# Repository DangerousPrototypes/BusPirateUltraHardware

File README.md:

# BusPirateUltraHardware
Schematic and PCBs for Bus Pirate Ultra

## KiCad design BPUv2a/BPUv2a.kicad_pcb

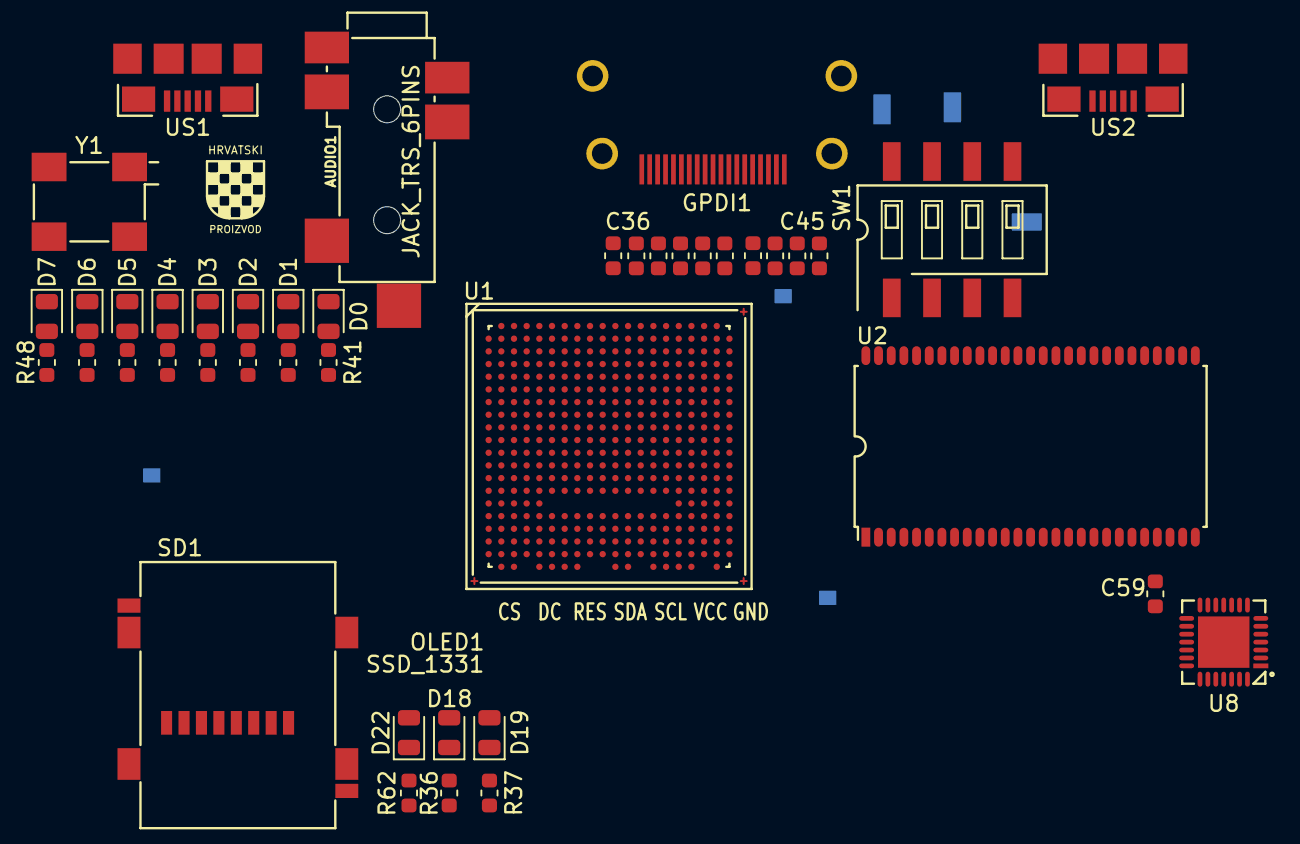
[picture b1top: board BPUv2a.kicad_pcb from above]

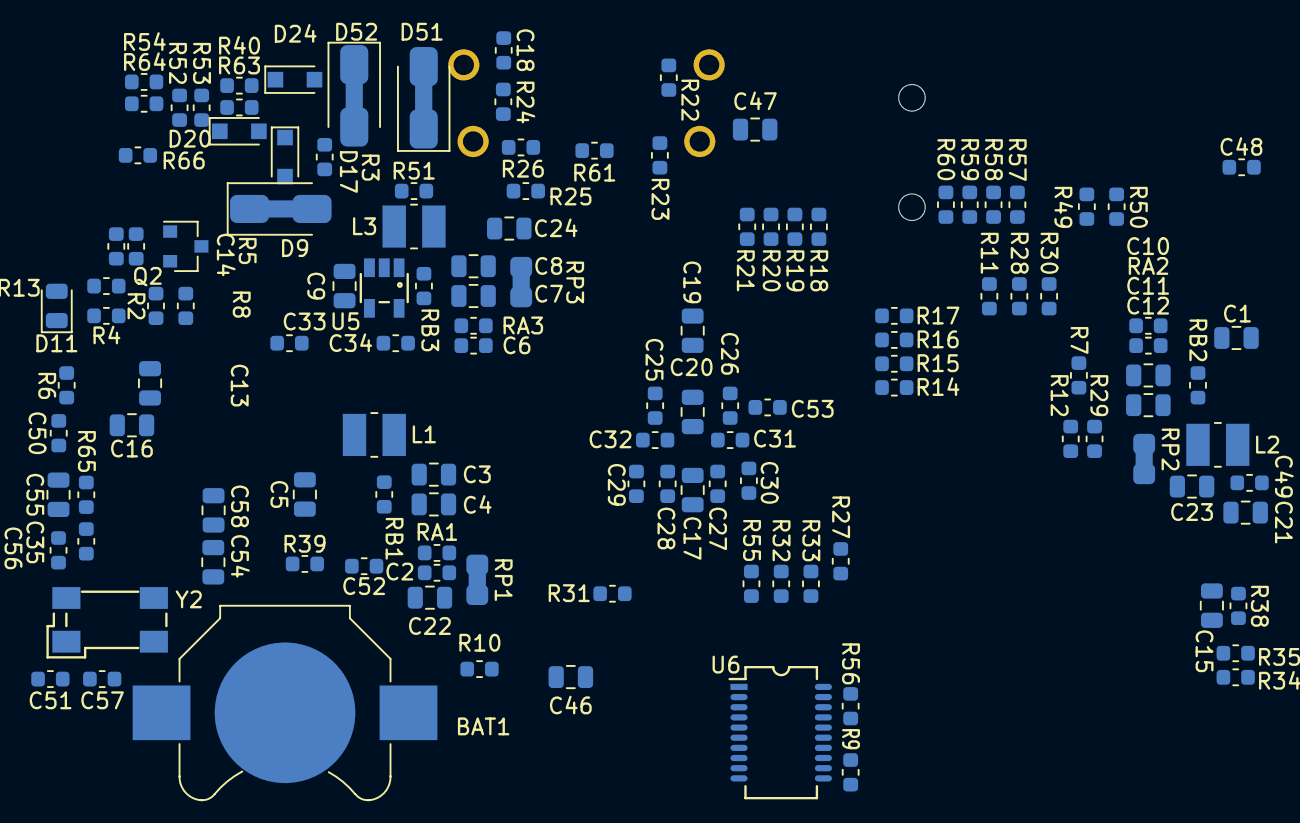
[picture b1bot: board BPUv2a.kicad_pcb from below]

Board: 4 copper layers, 171 parts (126 on the bottom side), 188 nets, no tracks yet.

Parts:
AUDIO1: JACK_TRS_6PINS; CUI_SJ-43516-SMT
BAT1: CR1225; Keystone_3000_1x12mm-CoinCell
C1, C3, C4, C5, C7, C8, C9, C11, C12, C15, C21, C54, C55, C58: 22uF; C_0805_2012Metric
C2, C6, C10, C18: 470pF; C_0603_1608Metric
C13, C16, C17, C19, C20, C22, C23, C24, C46, C47: 2.2uF; C_0805_2012Metric
C14, C36, C37, C38, C39, C40, C41, C42, C43, C44, C45, C59: 220nF; C_0603_1608Metric
C25, C26, C27, C28, C29, C30, C31, C32, C33, C34, C35, C48, C49, C50, C51, C52, C53: 22nF; C_0603_1608Metric
C56, C57: 3.3pF; C_0603_1608Metric
D0, D4, D11, D19: RED; LED_0805_2012Metric
D1, D5: ORANGE; LED_0805_2012Metric
D2, D6, D18: GREEN; LED_0805_2012Metric
D3, D7, D22: BLUE; LED_0805_2012Metric
D9, D51, D52: 0; D_SMA_Jumper_NC
D17, D24: 1N914; D_SOD-323_HandSoldering
D20: 3.6V; D_SOD-323_HandSoldering
GPDI1: GPDI-D; CONN-10029449-111RLF
HR: HR; hrvatski
L1, L2, L3: 2.2uH; L_1008_1210
OLED1: SSD_1331; oled_13xx
Q2: 2N7002; SOT-23
R2: 18k; R_0603_1608Metric
R3, R4, R25, R26, R30: 4.7k; R_0603_1608Metric
R5: 2.2M; R_0603_1608Metric
R6, R8, R14, R18, R29, R40, R54, R57, R66: 1.1k; R_0603_1608Metric
R7, R10, R17, R21, R39, R51, R60: 130; R_0603_1608Metric
R9, R13, R31, R32, R33, R34, R55, R63, R64: 15k; R_0603_1608Metric
R11, R12, R27, R28: 10k; R_0603_1608Metric
R15, R19, R35, R36, R37, R41, R42, R43, R44, R45, R46, R47, R48, R58, R61, R62, R65: 549; R_0603_1608Metric
R16, R20, R59: 270; R_0603_1608Metric
R22, R23: 3.3k; R_0603_1608Metric
R24: 100k; R_0603_1608Metric
R38: 0.47; R_0603_1608Metric
R49, R50, R52, R53: 27; R_0603_1608Metric
R56: 0; R_0603_1608Metric
RA1, RA2, RA3: 15k; R_0603_1608Metric
RB1: 18k; R_0603_1608Metric
RB2: 4.7k; R_0603_1608Metric
RB3: 3.3k; R_0603_1608Metric
RP1, RP2, RP3: 0; R_0805_2012Metric_Pad1.29x1.40mm_HandSolder_Jumper_NC
SD1: SCHD3A0100; SCHD3A100
SW1: SW_DIP_x04; SW_DIP_x4_W8.61mm_Slide_LowProfile
U1: LFE5U-85F-6BG381C; BGA-381_pitch0.8mm_dia0.4mm
U2: MT48LC16M16A2TG; TSOP54
U5: TLV62569DBV; TSOT-25
U6: FT231XS; FT231X-SSOP-20_4.4x6.5mm_Pitch0.65mm
U8: MAX11125; MAX1112x-TQFN-28-1EP_5x5mm_Pitch0.5mm
US1, US2: MICRO_USB; USB-MICRO-B-FCI-10118192-0001LF
Y1: FNETHE025; Crystal_SMD_7050_4Pads
Y2: 32768Hz; Crystal_SMD_ABS25

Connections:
2V5_3V3: C26.1, C47.1, C48.1, C49.1, C53.1, R51.1, U1.F9, U1.F10, U1.H6, U1.H7, U1.J6
+1V1: C17.1, C27.1, C28.1, RP1.2, U1.H8, U1.H9, U1.H10, U1.H11, U1.H12, U1.H13, U1.J8, U1.J13, U1.K8, U1.K13, U1.L8, U1.L13, U1.M8, U1.M13, U1.N8, U1.N9, U1.N10, U1.N11, U1.N12, U1.N13
+2V5: C19.1, C29.1, C30.1, R22.1, R23.1, RP2.2, U1.F6, U1.F15, U1.P6, U1.P15
+3V3: C16.1, C20.1, C21.1, C25.1, C31.1, C32.1, C33.1, C34.1, C35.1, C46.1, C50.1, C51.1, C52.1, D11.2, R7.1, R11.1, R12.1, R27.1, R28.1, R29.1, R30.1, R31.1, R32.1, R33.1, R34.1, R38.2, R39.1, R65.1, RP3.2, U1.F11, U1.F12, U1.H14, U1.H15, U1.J15, U1.L6, U1.L7, U1.L14, U1.L15, U1.M6, U1.M15, U1.P9, U1.P10, U1.T2, U1.T3, U1.T4, U1.U2, U2.1, U2.3, U2.9, U2.14, U2.27, U2.43, U2.49, Y1.1, Y1.4
+5V: C1.1, C5.1, C9.1, C13.1, D9.2, D51.1, D52.2, GPDI1.18, R3.1, R24.1, R25.1, R26.1, U5.4
/analog/ADC3V3: C58.1, C59.1, U8.15, U8.17, U8.18
/analog/AUDIO_L: AUDIO1.2, R14.2, R15.2, R16.2, R17.2
/analog/AUDIO_R: AUDIO1.3, R18.2, R19.2, R20.2, R21.2
/analog/AUDIO_V: AUDIO1.4, R57.2, R58.2, R59.2, R60.2
/blinkey/ALED0: D0.2, R41.2
/blinkey/ALED1: D1.2, R42.2
/blinkey/ALED2: D2.2, R43.2
/blinkey/ALED3: D3.2, R44.2
/blinkey/ALED4: D4.2, R45.2
/blinkey/ALED5: D5.2, R46.2
/blinkey/ALED6: D6.2, R47.2
/blinkey/ALED7: D7.2, R48.2
/blinkey/LED_PWREN: D18.1, R36.1
/blinkey/LED_TXLED: D19.1, R37.2
/blinkey/LED_WIFI: D22.1, R62.1
/blinkey/SWPU: R51.2, SW1.1, SW1.2, SW1.3, SW1.4
/flash/FLASH_MISO: R28.2, U1.V2
/flash/FLASH_MOSI: R27.2, U1.W2
/flash/FLASH_SCK: R29.2, U1.U3
/flash/FLASH_nCS: R30.2, U1.R2
/flash/FLASH_nHOLD: R12.2, U1.W1
/flash/FLASH_nWP: R11.2, U1.Y2
/flash/FPGA_DONE: R32.2, R55.1, U1.Y3
/flash/FPGA_INITN: R33.2, U1.V3
/flash/FPGA_PROGRAMN: R31.2, U1.W3
/gpdi/FPDI_CEC: R61.2, U1.A18
/gpdi/GPDI_CLK+: C45.2, GPDI1.10
/gpdi/GPDI_CLK-: C41.2, GPDI1.12
/gpdi/GPDI_D0+: C44.2, GPDI1.7
/gpdi/GPDI_D0-: C40.2, GPDI1.9
/gpdi/GPDI_D1+: C43.2, GPDI1.4
/gpdi/GPDI_D1-: C39.2, GPDI1.6
/gpdi/GPDI_D2+: C42.2, GPDI1.1
/gpdi/GPDI_D2-: C38.2, GPDI1.3
/gpdi/GPDI_ETH+: C36.2, GPDI1.14
/gpdi/GPDI_ETH-: C37.2, GPDI1.19
/gpdi/VREF2: C18.1, R24.2
/power/FB1: C2.2, RA1.2, RB1.2
/power/FB2: C10.2, RA2.2, RB2.2
/power/FB3: C6.2, RA3.2, RB3.2, U5.5
/power/HOLD: D11.1, R4.1
/power/L3: L3.1, U5.3
/power/OSCI_32k: C56.2, Y2.4
/power/OSCO_32k: C57.2, Y2.1
/power/P1V1: C2.1, C3.1, C4.1, C22.1, L1.2, RA1.1, RP1.1
/power/P2V5: C10.1, C11.1, C12.1, C23.1, L2.2, RA2.1, RP2.1
/power/P3V3: C6.1, C7.1, C8.1, C24.1, L3.2, RA3.1, RP3.1
/power/PWREN: R2.1, R4.2, R8.1, U5.1
/power/RTCVDD: C55.1, R65.2
/power/SHD: Q2.3, R8.2
/power/SHUT: C14.1, Q2.1, R5.1
/power/VBAT: BAT1.1, C54.1
/sdcard/SD3V3: C15.1, R38.1, SD1.4
/usb/FPD+: R53.2, US2.3
/usb/FPD-: R52.2, US2.2
/usb/FTD+: R50.2, US1.3
/usb/FTD-: R49.2, US1.2
/usb/US2VBUS: D9.1, US2.1
ADC_CSn: U1.R17, U8.20
ADC_MISO: U1.U16, U8.24
ADC_MOSI: U1.R16, U8.21
ADC_SCLK: U1.P17, U8.19
AUDIO_L0: R14.1, U1.E4
AUDIO_L1: R15.1, U1.D3
AUDIO_L2: R16.1, U1.C3
AUDIO_L3: R17.1, U1.B3
AUDIO_R0: R18.1, U1.A3
AUDIO_R1: R19.1, U1.B5
AUDIO_R2: R20.1, U1.D5
AUDIO_R3: R21.1, U1.C5
AUDIO_V0: R57.1, U1.H5
AUDIO_V1: R58.1, U1.F2
AUDIO_V2: R59.1, U1.F5
AUDIO_V3: R60.1, U1.E5
BTN_PWRn: D17.2, U1.D6
CLK_25MHz: U1.G2, Y1.3
FPDI_CLK+: C45.1, U1.A17
FPDI_CLK-: C41.1, U1.B18
FPDI_D0+: C44.1, U1.A16
FPDI_D0-: C40.1, U1.B16
FPDI_D1+: C43.1, U1.A14
FPDI_D1-: C39.1, U1.C14
FPDI_D2+: C42.1, U1.A12
FPDI_D2-: C38.1, U1.A13
FPDI_ETH+: C36.1, U1.A19
FPDI_ETH-: C37.1, U1.B20
FPDI_SCL: R23.2, U1.E12
FPDI_SDA: R22.2, U1.B19
FT2V5: D19.2, R9.2, U6.3, U6.13
FTDI_RXD: U1.L4, U6.4
FTDI_TXD: U1.M1, U6.20
FTDI_TXDEN: R56.2, U1.L3, U6.18
FTDI_nDTR: U1.N1, U6.1
FTDI_nRTS: U1.M3, U6.2
FTDI_nRXLED: U1.L5, U6.17
FTDI_nSLEEP: D18.2, R10.2, U6.19
FTDI_nTXLED: R37.1, U6.10
GN14: U1.U17, U8.26
GN15: U1.P16, U8.28
GN16: U1.M17, U8.2
GN17: U1.L17, U8.4
GND: AUDIO1.1, BAT1.2, C1.2, C3.2, C4.2, C5.2, C7.2, C8.2, C9.2, C11.2, C12.2, C14.2, C15.2, C16.2, C17.2, C18.2, C19.2, C20.2, C21.2, C22.2, C23.2, C24.2, C25.2, C26.2, C27.2, C28.2, C29.2, C30.2, C31.2, C32.2, C33.2, C34.2, C35.2, C46.2, C47.2, C48.2, C49.2, C50.2, C51.2, C52.2, C53.2, C54.2, C55.2, C56.1, C57.1, C58.2, C59.2, D0.1, D1.1, D2.1, D3.1, D4.1, D5.1, D6.1, D7.1, D20.2, GPDI1.0, GPDI1.2, GPDI1.5, GPDI1.8, GPDI1.11, GPDI1.17, Q2.2, R2.2, R5.2, R13.2, R36.2, R56.1, R62.2, RB1.1, RB2.1, RB3.1, SD1.6, SD1.9, SD1.10, SD1.11, U1.B7, U1.B14, U1.C19, U1.D4, U1.F7, U1.F8, U1.F13, U1.F14, U1.G4, U1.G6, U1.G7, U1.G8, U1.G9, U1.G10, U1.G11, U1.G12, U1.G13, U1.G14, U1.G15, U1.G17, U1.H19, U1.J2, U1.J7, U1.J9, U1.J10, U1.J11, U1.J12, U1.J14, U1.K6, U1.K7, U1.K9, U1.K10, U1.K11, U1.K12, U1.K14, U1.K15, U1.L9, U1.L10, U1.L11, U1.L12, U1.M2, U1.M7, U1.M9, U1.M10, U1.M11, U1.M12, U1.M14, U1.M16, U1.N6, U1.N7, U1.N14, U1.N15, U1.P7, U1.P8, U1.P11, U1.P12, U1.P13, U1.P14, U1.R4, U1.R19, U1.T6, U1.T7, U1.T8, U1.T9, U1.T10, U1.T11, U1.T12, U1.T13, U1.T14, U1.T15, U1.U4, U1.U6, U1.U7, U1.U8, U1.U9, U1.U10, U1.U11, U1.U12, U1.U13, U1.U14, U1.U15, U1.V5, U1.V6, U1.V7, U1.V8, U1.V9, U1.V10, U1.V11, U1.V12, U1.V13, U1.V14, U1.V15, U1.V16, U1.V17, U1.V18, U1.V19, U1.V20, U1.W6, U1.W7, U1.W12, U1.W15, U1.W16, U1.W19, U1.W20, U1.Y5, U1.Y6, U1.Y7, U1.Y8, U1.Y11, U1.Y12, U1.Y14, U1.Y15, U1.Y16, U1.Y17, U1.Y19, U2.6, U2.12, U2.28, U2.41, U2.46, U2.52, U2.54, U5.2, U6.6, U6.16, U8.6, U8.7, U8.8, U8.9, U8.10, U8.11, U8.13, U8.14, U8.16, U8.22, U8.29, US1.5, US1.6, US2.5, US2.6, Y1.2
GP14: U1.U18, U8.27
GP15: U1.N17, U8.1
GP16: U1.N16, U8.3
GP17: U1.L16, U8.5
GPDI_CEC: GPDI1.13, R61.1
GPDI_SCL: GPDI1.15, R25.2
GPDI_SDA: GPDI1.16, R26.2
JTAG_TCK: U1.T5, U6.7
JTAG_TDI: U1.R5, U6.5
JTAG_TDO: U1.V4, U6.9
JTAG_TMS: U1.U5, U6.8
LED0: R41.1, U1.B2
LED1: R42.1, U1.C2
LED2: R43.1, U1.C1
LED3: R44.1, U1.D2
LED4: R45.1, U1.D1
LED5: R46.1, U1.E2
LED6: R47.1, U1.E1
LED7: R48.1, U1.H3
unnamed: D24.1, R40.1
PWRBTn: D17.1, R3.2
SDRAM_A0: U1.M20, U2.23
SDRAM_A1: U1.M19, U2.24
SDRAM_A2: U1.L20, U2.25
SDRAM_A3: U1.L19, U2.26
SDRAM_A4: U1.K20, U2.29
SDRAM_A5: U1.K19, U2.30
SDRAM_A6: U1.K18, U2.31
SDRAM_A7: U1.J20, U2.32
SDRAM_A8: U1.J19, U2.33
SDRAM_A9: U1.H20, U2.34
SDRAM_A10: U1.N19, U2.22
SDRAM_A11: U1.G20, U2.35
SDRAM_A12: U1.G19, U2.36
SDRAM_BA0: U1.P19, U2.20
SDRAM_BA1: U1.N20, U2.21
SDRAM_CKE: U1.F20, U2.37
SDRAM_CLK: U1.F19, U2.38
SDRAM_D0: U1.J16, U2.2
SDRAM_D1: U1.L18, U2.4
SDRAM_D2: U1.M18, U2.5
SDRAM_D3: U1.N18, U2.7
SDRAM_D4: U1.P18, U2.8
SDRAM_D5: U1.T18, U2.10
SDRAM_D6: U1.T17, U2.11
SDRAM_D7: U1.U20, U2.13
SDRAM_D8: U1.E19, U2.42
SDRAM_D9: U1.D20, U2.44
SDRAM_D10: U1.D19, U2.45
SDRAM_D11: U1.C20, U2.47
SDRAM_D12: U1.E18, U2.48
SDRAM_D13: U1.F18, U2.50
SDRAM_D14: U1.J18, U2.51
SDRAM_D15: U1.J17, U2.53
SDRAM_DQM0: U1.U19, U2.15
SDRAM_DQM1: U1.E20, U2.39
SDRAM_nCAS: U1.T19, U2.17
SDRAM_nCS: U1.P20, U2.19
SDRAM_nRAS: U1.R20, U2.18
SDRAM_nWE: U1.T20, U2.16
SD_CLK: SD1.5, U1.H2
SD_CMD: SD1.3, U1.J1
SD_D0: SD1.7, U1.J3
SD_D1: SD1.8, U1.H1
SD_D2: SD1.1, U1.K1
SD_D3: SD1.2, U1.K2
SHUTDOWN: R13.1, U1.G16
SW1: SW1.8, U1.E8
SW2: SW1.7, U1.D8
SW3: SW1.6, U1.D7
SW4: SW1.5, U1.E7
US2_ID: R66.1, US2.4
USB5V: U6.15, US1.1
USB_FPGA_D+: D20.1, R40.2, R53.1, R63.2, U1.D15, U1.E16
USB_FPGA_D-: R52.1, R54.1, R64.2, U1.E15, U1.F16
USB_FPGA_PULL_D+: D24.2, U1.B12
USB_FTDI_D+: R50.1, U6.11
USB_FTDI_D-: R49.1, U6.12
WIFI_EN: R34.2, R35.1, U1.F1
WIFI_GPIO5: D22.2, U1.N4
nRESET: R9.1, U6.14

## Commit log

2019-08-26 initial check in from old repo https://github.com/DangerousPrototypes/Bus_Pirate_Ultra
2019-08-26 spreadsheets for calculating margining on the Vreg
2019-08-28 continue routing
2019-08-28 routed power traces
2019-08-29 board routing done, add usbc bottom PTH chassis mount library
2019-08-30 creted gerber for v1b
2019-09-06 added BP 'sail' daughter board
2019-09-06 make IO connector protrusion clearance to 1.5mm
2019-09-06 add DWG reference
2019-09-10 added vout and GND test point. add LED status to vout
2019-09-10 created geber for BPU display
2019-09-11 fix testboard IO header to match v1b, created gerbers
2019-09-24 new BPUltra.v.1.0C revision broke RN3 to individual 10K R603 resistors Added 1uF 0603 cap to U14 connect OE and DIR of latch (245) to FPGA Change values of the following parts: R27 to 100K R32 to 10K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
2019-10-03 fix bom parts naming change back to original SC-70-5 and SC-70-6 footprints for 74LVC1G07DBV and SN74LVC1T45DBV added decoupling caps for open drain buffers(on going)
2019-10-04 Revert previous commit to v1b, wrong version commited. changes should be on v1c not v1b.
    This reverts commit d10a26b079303959180bb4ab2616075854f9b9d1.
2019-10-05 new BPUltra.v.1.0C revision removed some text labels renamed BPIO pin labels fix bom parts naming change back to original SC-70-5 and SC-70-6 footprints for 74LVC1G07DBV and SN74LVC1T45DBV added deco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
2019-10-05 re-number parts logically changed C302 to 1uF add 4.7uF input cap on VR1 add 4.7uF input cap on VR2 add RC filter 25R and 1.5nF on ADC MUX buffer
2019-10-10 added ADC ADS7041 and wired to FPGA pin 45, 47 and 48 changed 3.3V regulator to bigger MCP1700 changed mux to 16-bit version 74HCT4067, added one new address line S3 to FPGA (not connected yet) conne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
2019-10-10 change supply of ADC chip to 3.3V
2019-10-15 updates on v1c schematic moved MCU_VPU to PA9, free up A10 moved DISPLAY_CS to PF11 (former DISPLAY_D/P) and DISPLAY_D/P to PB1, free up A6 moved FPGA MCU_INT1 from GBIN5 to FPGA pin 115 wired PG8 to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
2019-10-15 renamed DISPLAY_AUX2 to DISPLAY_AUX1 connected to PB1 renamed DISPLAY_AUX1 to DISPLAY_RESET and connected to PB2/BOOT1, wired a pull down resistor too rewired DISPLAY_CS from PF11 to PC4 rewired DISP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
2019-10-15 rewiring of v1c schematic continues
    renamed MCU_AUX7 to MCU_INT0
    renamed MCU_AUX8 to MCU_INT1
    renamed MCU_INT0 to MCU_PWM0
    renamed PWM to MCU_PWM1
    moved LAT_OE to FPGA pin 96
    moved LAT_DIR to FPGA pin 95
2019-10-16 continued on v1c schematic changes renamed MCU_AUX4 to MCU_INT3 and move it from MCU PD6 to PD2 renamed MCU_INT1I to MCU_AUX0 fix display connections
2019-10-16 continue on v1c schematic revisions -removed net DISPLAY_CSI on MCU pin 49 -renamed MCU_AUX5 to MCU_AUX4 and MCU_AUX6 to MCU_AUX5 -renamed MCU_ADC5 to MCU_ADC2 -renamed MCU_ADC6 to MCU_ADC3 -wired MC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
2019-10-20 finishing up routing on v1c board
2019-10-22 change display connector to FPC connector, done routing
2019-11-02 update reference dwg
2019-12-14 display board, fonts, 25lc eeprom breakout test board
2019-12-14 display board reorganization.
2020-04-21 preliminary commit of Bus Pirate Ultra v2, additional designs attribute to ULX3s https://github.com/emard/ulx3s and Butterstick https://github.com/gregdavill/ButterStick
2020-06-01 added 3d model of bus pirate ultra v1 case in freecad
2021-04-13 Added boxy corner version of the case on v1.1
2021-04-14 added v1.2 case, revert usb port back to rounded corner hole
